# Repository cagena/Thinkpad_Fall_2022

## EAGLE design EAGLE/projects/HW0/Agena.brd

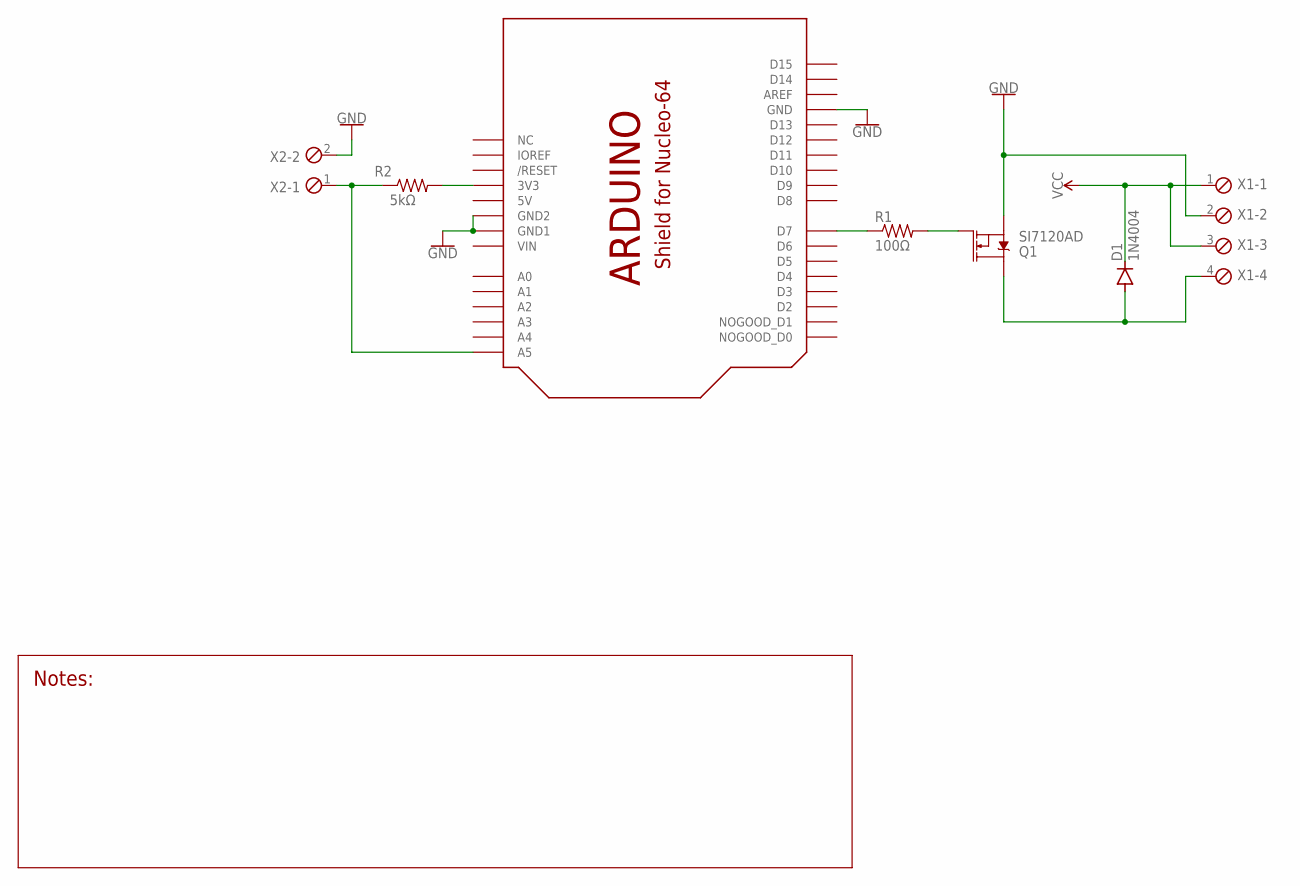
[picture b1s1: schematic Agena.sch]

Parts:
D1: 1N4004; DO41-10
Q1: SI7120AD; 1212-8
R1: 100Ω; R0805
R2: 5kΩ; M0805
U$1: SHIELD_FOR_NUCLE0_64_SHORT; SHIELD_FOR_NUCLEO_64_SHORT
X1: SCREWTERM_4P_381; 4POL381
X2: SCREWTERM_2P_254; 2POL254

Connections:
5V: U$1.5V
GND: Q1.1 (S), Q1.2 (S), Q1.3 (S), U$1.GND, U$1.GND1, U$1.GND2, X1.2, X2.2
unnamed: R1.1, U$1.D7
unnamed: Q1.4 (G), R1.2
unnamed: D1.A, Q1.5 (D), Q1.6 (D), Q1.7 (D), Q1.8 (D), Q1.PAD (D), X1.4
unnamed: R2.2, U$1.3V (3V3)
unnamed: R2.1, U$1.A5, X2.1
VCC: D1.C, X1.1, X1.3
VIN: U$1.VIN

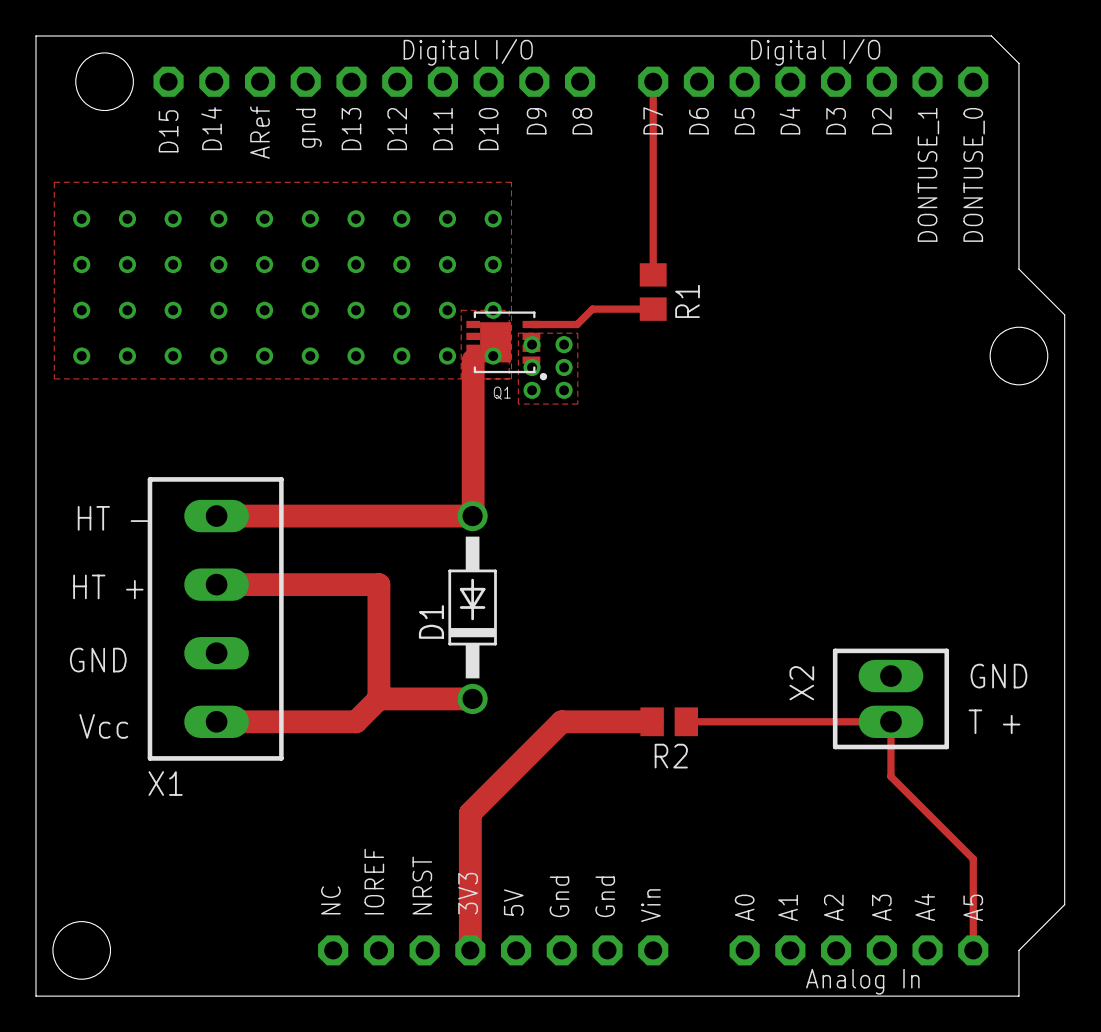
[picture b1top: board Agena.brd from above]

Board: 2 copper layers, 57.1 x 53.3 mm, 7 parts (0 on the bottom side), 7 nets.

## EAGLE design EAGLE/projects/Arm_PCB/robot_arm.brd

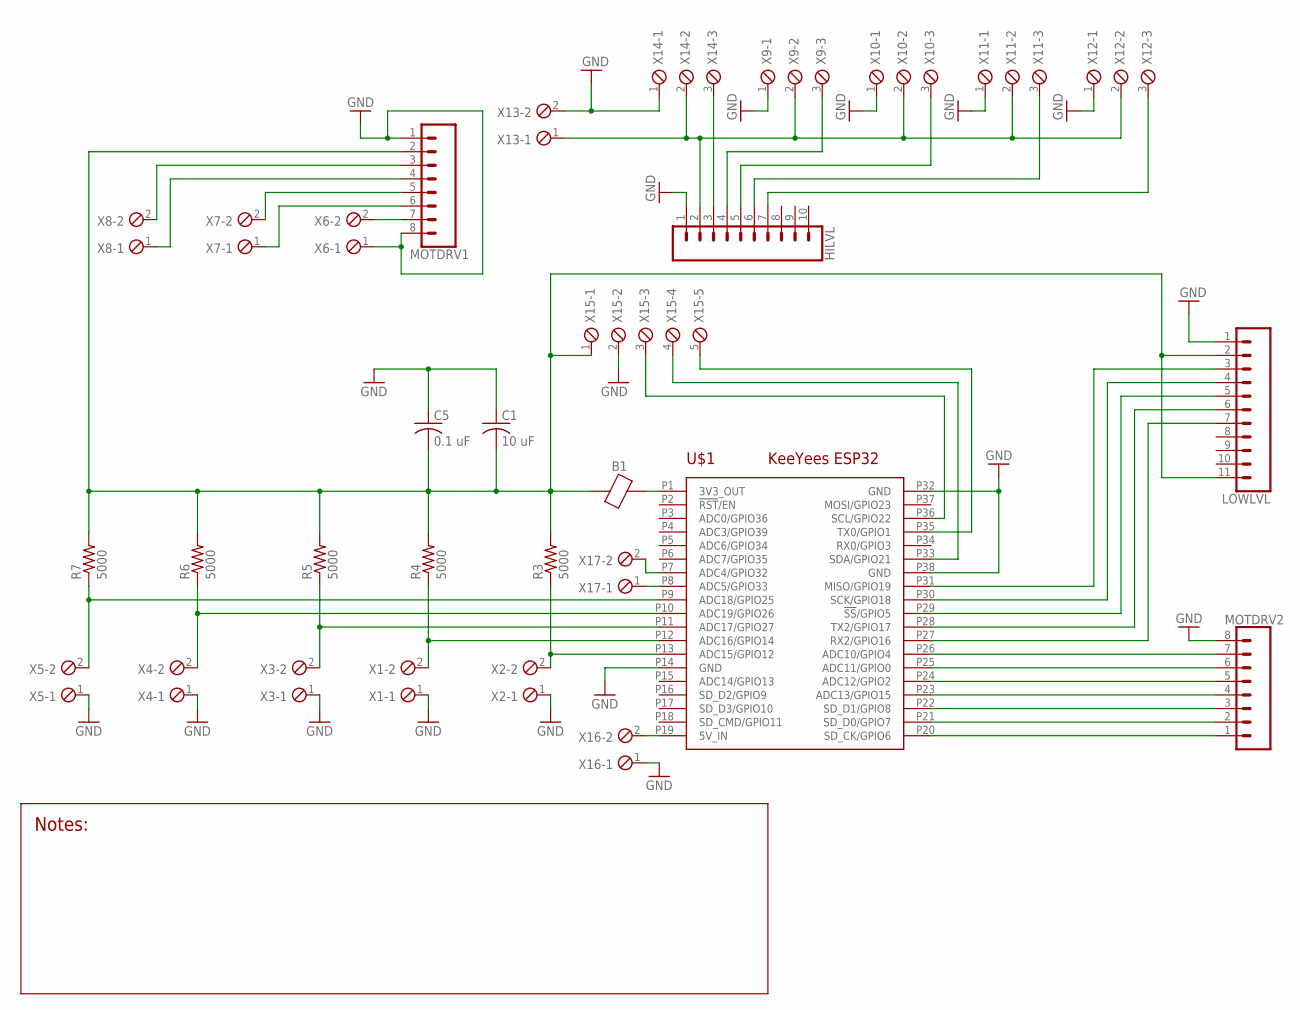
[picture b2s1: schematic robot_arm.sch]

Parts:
B1: BEAD0805; 0805
C1: 10 uF; C0805
C5: 0.1 uF; C0805
HILVL: CONN_10"; 1X10
LOWLVL: CONN_11; 1X11
MOTDRV1, MOTDRV2: CONN_08"; 1X08
R3, R4, R5, R6, R7: 5000; R0805
U$1: KEEYEES_ESP32EXT; KEEYEES_ESP32_EXTENDED
X1, X2, X3, X4, X5, X6, X7, X8, X13, X16, X17: SCREWTERM_2P_254; 2POL254
X9, X10, X11, X12, X14: SCREWTERM_3P_254; 3POL254
X15: SCREWTERM_5P_254; 5POL254

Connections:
AIN1: MOTDRV2.3, U$1.P22 (SD_D1/GPIO8)
AIN2: MOTDRV2.2, U$1.P21 (SD_D0/GPIO7)
AO1: MOTDRV1.3, X8.2
AO2: MOTDRV1.4, X8.1
BIN1: MOTDRV2.5, U$1.P24 (ADC12/GPIO2)
BIN2: MOTDRV2.6, U$1.P25 (ADC11/GPIO0)
BO1: MOTDRV1.6, X7.1
BO2: MOTDRV1.5, X7.2
GND: C1.1, C5.1, HILVL.1, LOWLVL.1, MOTDRV1.1, MOTDRV1.8, MOTDRV2.8, U$1.P14 (GND), U$1.P32 (GND), U$1.P38 (GND), X1.1, X2.1, X3.1, X4.1, X5.1, X6.1, X9.1, X10.1, X11.1, X12.1, X13.2, X14.1, X15.2, X16.1
unnamed: R3.1, U$1.P13 (ADC15/GPIO12), X2.2
unnamed: R4.1, U$1.P12 (ADC16/GPIO14), X1.2
unnamed: B1.2, U$1.P1 (3V3_OUT)
unnamed: U$1.P36 (SCL/GPIO22), X15.3
unnamed: U$1.P33 (SDA/GPIO21), X15.4
unnamed: R5.1, U$1.P11 (ADC17/GPIO27), X3.2
unnamed: R6.1, U$1.P10 (ADC19/GPIO26), X4.2
unnamed: U$1.P35 (TX0/GPIO1), X15.5
unnamed: R7.1, U$1.P9 (ADC18/GPIO25), X5.2
unnamed: U$1.P19 (5V_IN), X16.2
unnamed: U$1.P8 (ADC5/GPIO33), X17.1
unnamed: U$1.P7 (ADC4/GPIO32), X17.2
unnamed: HILVL.3, X14.3
unnamed: HILVL.4, X9.3
unnamed: HILVL.5, X10.3
unnamed: HILVL.6, X11.3
unnamed: HILVL.7, X12.3
unnamed: LOWLVL.3, U$1.P31 (MISO/GPIO19)
unnamed: LOWLVL.4, U$1.P30 (SCK/GPIO18)
unnamed: LOWLVL.5, U$1.P29 (!SS!/GPIO5)
unnamed: LOWLVL.6, U$1.P28 (TX2/GPIO17)
unnamed: LOWLVL.7, U$1.P27 (RX2/GPIO16)
unnamed: HILVL.2, X9.2, X10.2, X11.2, X12.2, X13.1, X14.2
PWMA: MOTDRV2.1, U$1.P20 (SD_CK/GPIO6)
PWMB: MOTDRV2.7, U$1.P26 (ADC10/GPIO4)
STBY: MOTDRV2.4, U$1.P23 (ADC13/GPIO15)
VCC: B1.1, C1.2, C5.2, LOWLVL.2, LOWLVL.11, MOTDRV1.2, R3.2, R4.2, R5.2, R6.2, R7.2, X15.1
VMOT: MOTDRV1.7, X6.2

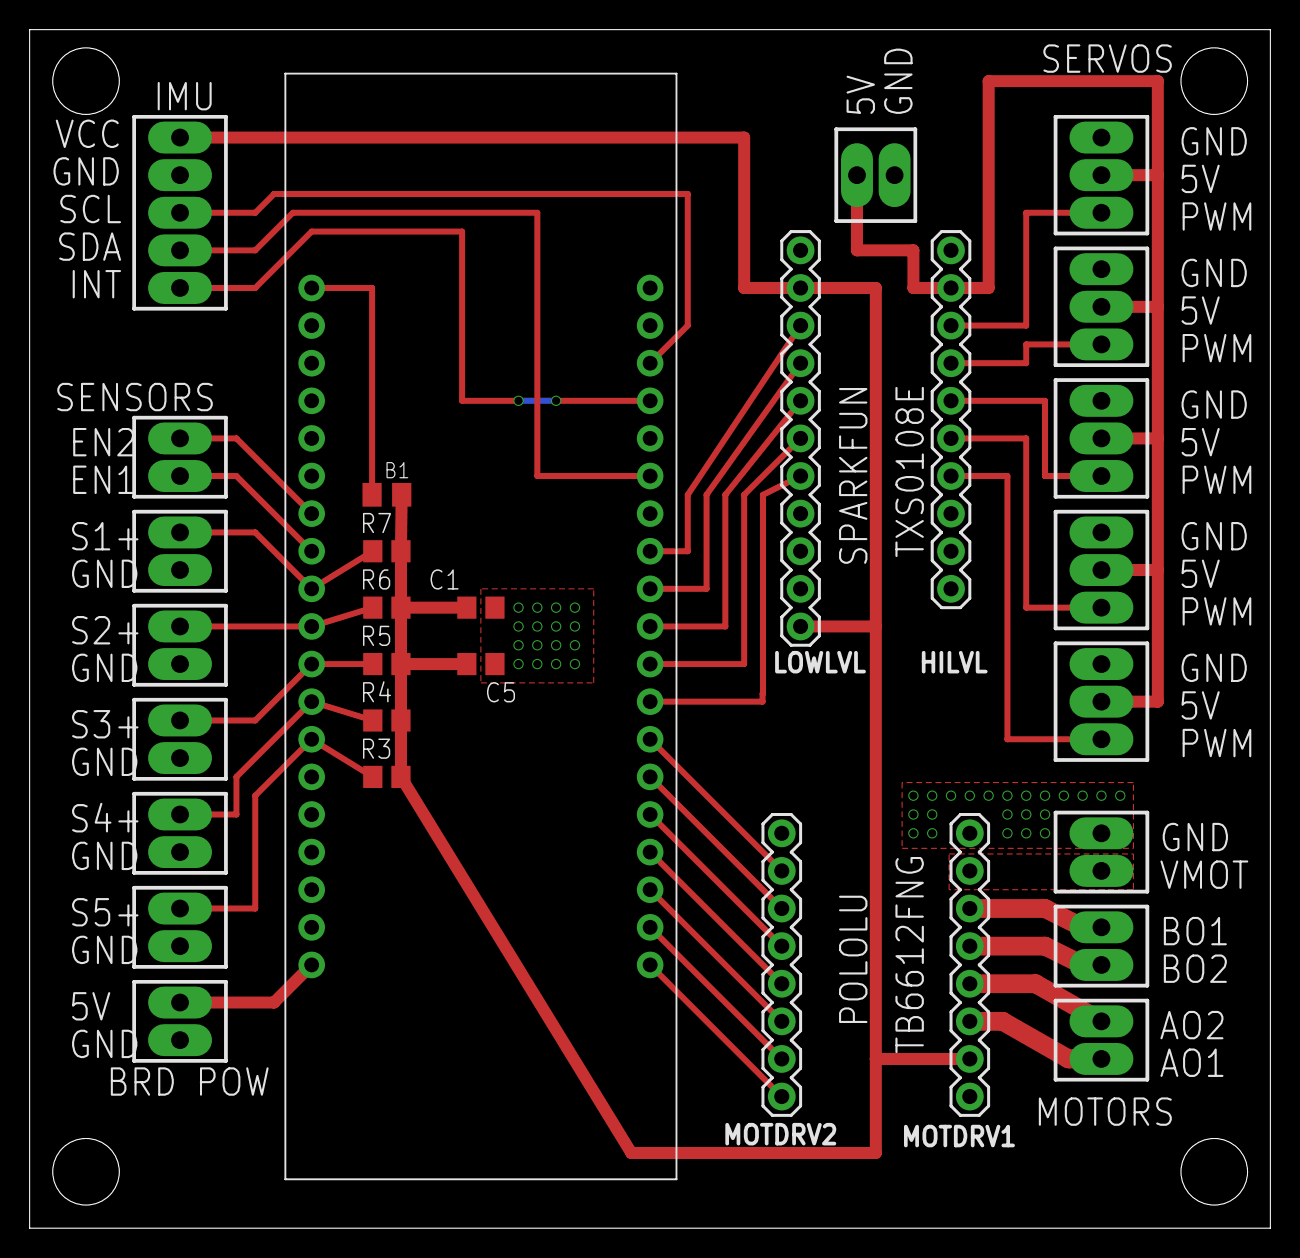
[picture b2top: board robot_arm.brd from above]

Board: 2 copper layers, 83.8 x 81.0 mm, 30 parts (0 on the bottom side), 37 nets.

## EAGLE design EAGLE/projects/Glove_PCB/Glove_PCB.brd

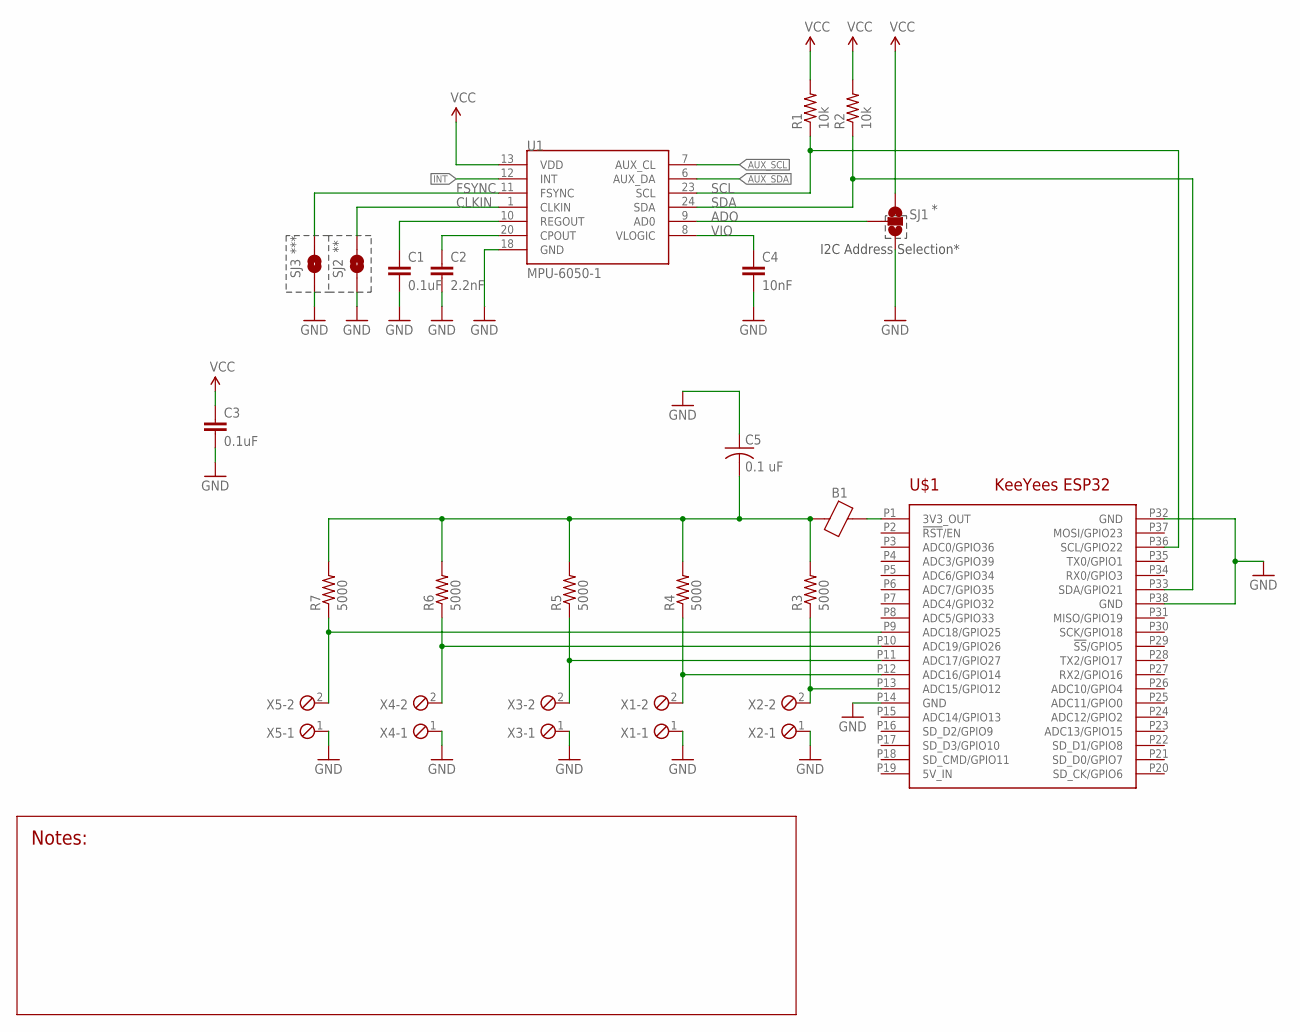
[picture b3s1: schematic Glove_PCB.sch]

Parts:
B1: BEAD0805; 0805
C1, C3: 0.1uF; 0603-CAP
C2: 2.2nF; 0603-CAP
C4: 10nF; 0603-CAP
C5: 0.1 uF; C0805
R1, R2: 10k; 0603-RES
R3, R4, R5, R6, R7: 5000; R0805
SJ1: SOLDERJUMPER_2WAYPASTE2&3; SJ_3_PASTE2&3
SJ2, SJ3: SOLDERJUMPERTRACE; SJ_2S-TRACE
U1: MPU-6050-1; QFN-24-4MM2
U$1: KEEYEES_ESP32EXT; KEEYEES_ESP32_EXTENDED
X1, X2, X3, X4, X5: SCREWTERM_2P_254; 2POL254

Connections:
5V_IN: U$1.P19 (5V_IN)
ADO: SJ1.2, U1.9 (AD0)
AUX_SCL: U1.7 (AUX_CL)
AUX_SDA: U1.6 (AUX_DA)
CLKIN: SJ2.2, U1.1 (CLKIN)
FSYNC: SJ3.2, U1.11 (FSYNC)
GND: C1.2, C2.2, C3.2, C4.2, C5.1, SJ1.3, SJ2.1, SJ3.1, U1.18 (GND), U$1.P14 (GND), U$1.P32 (GND), U$1.P38 (GND), X1.1, X2.1, X3.1, X4.1, X5.1
INT: U1.12 (INT)
unnamed: R3.1, U$1.P13 (ADC15/GPIO12), X2.2
unnamed: R4.1, U$1.P12 (ADC16/GPIO14), X1.2
unnamed: C2.1, U1.20 (CPOUT)
unnamed: B1.2, U$1.P1 (3V3_OUT)
unnamed: C1.1, U1.10 (REGOUT)
unnamed: R5.1, U$1.P11 (ADC17/GPIO27), X3.2
unnamed: R6.1, U$1.P10 (ADC19/GPIO26), X4.2
unnamed: R7.1, U$1.P9 (ADC18/GPIO25), X5.2
unnamed: B1.1, C5.2, R3.2, R4.2, R5.2, R6.2, R7.2
SCL: R1.1, U1.23 (SCL), U$1.P36 (SCL/GPIO22)
SDA: R2.1, U1.24 (SDA), U$1.P33 (SDA/GPIO21)
VCC: C3.1, R1.2, R2.2, SJ1.1, U1.13 (VDD)
VIO: C4.1, U1.8 (VLOGIC)

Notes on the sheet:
I2C Address Selection*
***

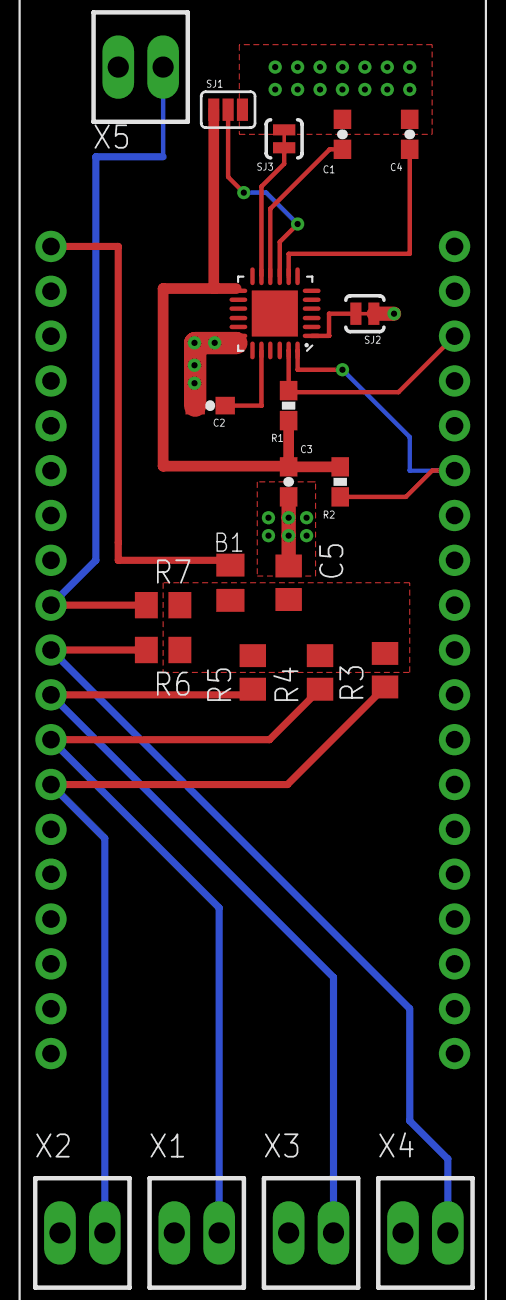
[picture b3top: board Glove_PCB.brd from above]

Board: 2 copper layers, 23 parts (0 on the bottom side), 17 nets.

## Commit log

2022-12-02 EAGLE

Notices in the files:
parts and their libraries:
SparkFun-Connectors: Licensing: Creative Commons ShareAlike 4.0 International - https://creativecommons.org/licenses/by-sa/4.0
